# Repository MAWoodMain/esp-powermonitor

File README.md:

# ESP32-S2 Based Power Meter
This projects sets out to create a standalone power meter with 4 current channels and a voltage channel, this unit should be able to take measurement and publish calibrated values over MQTT to homeassistant and other applications.
This design will focus on having a smaller package and power consumption then similar RPI based solutions like my earlier designs. This design will also integrate a battery backup system to data can be captured during supply drop outs.

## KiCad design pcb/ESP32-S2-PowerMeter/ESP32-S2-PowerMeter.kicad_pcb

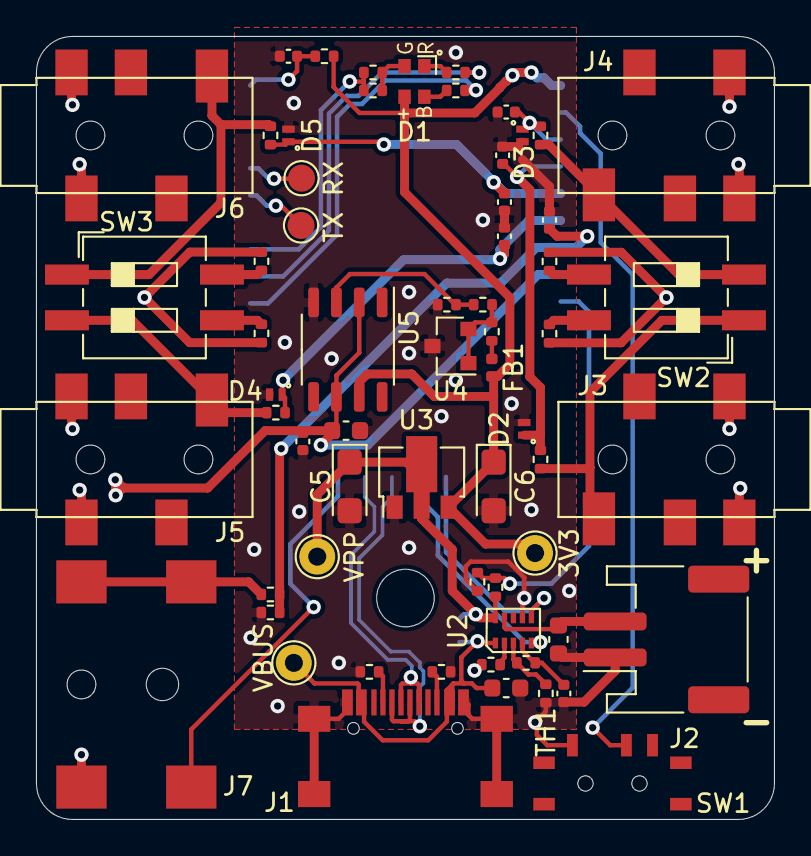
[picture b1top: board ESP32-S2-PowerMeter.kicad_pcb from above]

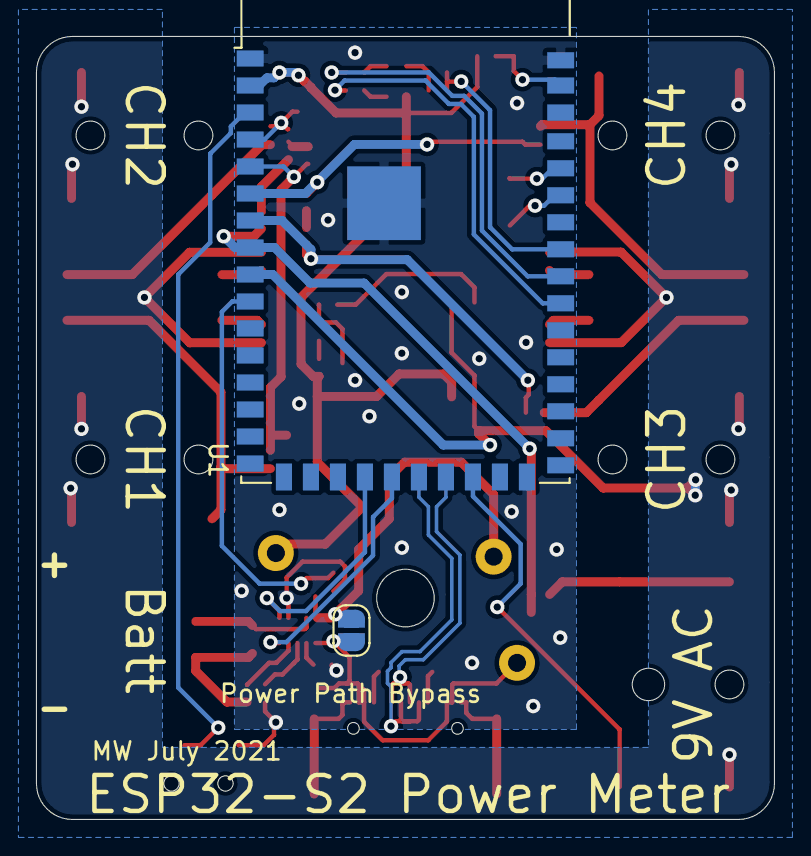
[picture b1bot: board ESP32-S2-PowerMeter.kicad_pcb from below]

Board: 2 copper layers, 41.0 x 43.5 mm, 66 parts (2 on the bottom side), 44 nets.

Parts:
C1, C2, C13: 1uF; C_0603_1608Metric
C3, C4, C7, C8, C9, C10, C11, C12: 100nF; C_0402_1005Metric
C5, C6: 10uF; CP_EIA-3216-18_Kemet-A
D1: FM-B2020RGBA-HG
D2, D3, D4, D5: ESD9B3.3ST5G; SMD-DFN1006
FB1: 600R@100MHz; L_0402_1005Metric
H1: MountingHole; MountingHole_3.2mm_M3
J1: USB_C_Receptacle_USB2.0; TYPEC-304S-ACP16
J2: Battery; JST_PH_S2B-PH-SM4-TB_1x02-1MP_P2.00mm_Horizontal
J3, J4, J5, J6: AudioJack3; PJ-327F
J7: AC In; DC-005-5A-2.0-SMT
JP1: Power Path Bypass; SolderJumper-2_P1.3mm_Open_RoundedPad1.0x1.5mm
R1: 150; R_0402_1005Metric
R2, R3, R4: 120R; R_0402_1005Metric
R5, R6: 5K1; R_0402_1005Metric
R7, R9, R10, R11, R13, R14, R15, R16, R17, R18: 10K; R_0402_1005Metric
R8: 1.1K; R_0402_1005Metric
R12: 560R; R_0402_1005Metric
R19, R20, R21, R22: Rb; R_0402_1005Metric
R23: 6.8K; R_0402_1005Metric
R24: 1K; R_0402_1005Metric
SW1: SW_SPDT; MSK12C02-HB
SW2, SW3: SW_DIP_x02; SW_DIP_SPSTx02_Slide_6.7x6.64mm_W8.61mm_P2.54mm_LowProfile
TH1: 10K NTC; R_0402_1005Metric
TP1: VBUS; TestPoint_THTPad_D2.0mm_Drill1.0mm
TP2: VPP; TestPoint_THTPad_D2.0mm_Drill1.0mm
TP3: 3V3; TestPoint_THTPad_D2.0mm_Drill1.0mm
TP4: RX; TestPoint_Pad_D1.5mm
TP5: TX; TestPoint_Pad_D1.5mm
U1: ESP32-S2-WROVER
U2: XC6806XXXX11-G; LGA-10B01
U3: XC6203E332PR; SOT-89-3
U4: CJ432; SOT-23
U5: LM741; SOP-8_3.9x4.9mm_P1.27mm

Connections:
+2V5: R12.2, R13.1, U4.1, U4.2
+3V3: C6.1, D1.3, FB1.1, R9.1, TP3.1, U1.2, U3.3, U5.7
+BATT: C2.2, J2.2, U2.9
AC_PLUG: J7.3, U1.24
BLUE: R4.2, U1.33
CH1_IN: C7.1, D2.1, R15.1, U1.5
CH2_IN: C8.1, D3.1, R16.1, U1.4
CH3_IN: C9.1, D4.1, R17.1, U1.7
CH4_IN: C10.1, D5.1, R18.1, U1.6
CHARGE_STATE: U1.20, U2.6
GND: C1.2, C2.1, C3.2, C4.2, C5.2, C6.2, C7.2, C8.2, C9.2, C10.2, C11.2, C12.2, C13.1, D2.2, D3.2, D4.2, D5.2, J1.A1, J1.A12, J1.B1, J1.B12, J1.S1, J2.1, R5.1, R6.1, R8.2, R11.2, R14.2, R24.2, SW1.3, TH1.2, U1.1, U1.26, U1.42, U1.43, U2.7, U3.1, U4.3, U5.4
GREEN: R2.2, R3.2, U1.35
unnamed: C3.1, R7.1, U2.4
unnamed: C4.1, R9.2, U1.41
unnamed: C5.1, JP1.2, R10.1, TP2.1, U2.10, U3.2
unnamed: D1.1, R1.1
unnamed: D1.2, R4.1
unnamed: D1.4, R2.1, R3.1
unnamed: FB1.2, R12.1
unnamed: J1.A5, R5.2
unnamed: J1.B5, R6.2
unnamed: J3.T, R15.2, SW2.1
unnamed: J4.T, R16.2, SW2.2
unnamed: J5.T, R17.2, SW3.2
unnamed: J6.T, R18.2, SW3.1
unnamed: J7.1, R23.1
unnamed: R7.2, TH1.1, U2.3
unnamed: R8.1, U2.2
unnamed: R13.2, R14.1, U5.3
unnamed: R19.1, SW2.4
unnamed: R20.2, SW2.3
unnamed: R21.1, SW3.3
unnamed: R22.2, SW3.4
unnamed: SW1.2, U1.3
unnamed: TP4.1, U1.38
unnamed: TP5.1, U1.37
POWER_GOOD: U1.21, U2.5
RED: R1.2, U1.34
REF_SENSE: C12.1, C13.2, J3.S, J4.S, J5.S, J6.S, J7.2, R19.2, R20.1, R21.2, R22.1, U1.9, U5.2, U5.6
USB_D+: J1.A6, J1.B6, U1.23
USB_D-: J1.A7, J1.B7, U1.22
VBUS: C1.1, J1.A4, J1.A9, J1.B4, J1.B9, JP1.1, TP1.1, U2.1
VPP_SENSE: R10.2, R11.1, U1.10
V_IN: C11.1, R23.2, R24.1, U1.8

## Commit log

2021-07-15 Initial commit, hello world example with basic LED driver and pinmap added
2021-07-17 Implemented a sampling system to sample the channels at 1khz and dispatch blocks of 1000 samples to a task for processing
2021-07-17 Moved most constants into a kconfig menu and added various configuration options
2021-07-17 Reformatted into structured file template to improve readability and cleaned up main
2021-07-17 Implemented basic RMS calculations
2021-07-18 Added current min and max, also added frequency measurement
2021-07-18 Added basic wifi and mqtt test code, also bumped WDT timeouts
2021-07-21 Added measurement condition and performed tweaks for real hardware, also increased app size to 1.5M with otafu but no factory image
2021-07-21 Organised wifi and mqtt into specific files and added a webserver for configuration (currently just hosting a demo static file)
2021-07-21 Added file system and setup json file to be loaded which contains the wifi and mqtt details
2021-07-24 Added battery system and started developing web interface, still WIP
2021-07-24 Added mqtt and wifi setting to the website
2021-07-24 Added calibration to web UI
2021-07-24 Added VA and P, also made the device write a default config file in
2021-07-24 Since the charger IC is misbehaving simplified batter reporting to charging/discharging
2021-07-24 Fixed bug where I cal did not work and also recals did not consider existing cal
2021-07-24 Reformatted website to put all data from a channel together
2021-07-24 Added cal reset button
2021-07-26 Added PCB to git
2021-07-26 Updated schematic - Added ESD diodes to USB and V sense - Fixed V sense input to be reference centered - Added jumper to choose between CJ431 and CJ432 - Replaced XC6806 with JLC assemble-able BQ2407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
2021-09-12 Added battery not fitted state
2021-09-12 Added module step file and re-exported assembly step file
2021-09-12 Added home assistant integration
